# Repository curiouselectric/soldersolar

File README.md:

# Solder Solar
Design and instructions for a simple DIY solar powered torch.

# Overview
This is a very simple soldering kit to build a solar powered torch.
The unit has a small solar panel which recharges an ultra-capacitor.
There are two LEDs, one white and one red, which are powered by the energy in the ultra-capacitor.

The ultra-capacitor is 0.47F which stores enough charge for around 20 mins of white light, or around 1 hour of red light.

This kit is designed as an introduction to solar power and also soldering.

This kit can also be used as a small power supply for other projects (requiring a 3-5.5V power supply). This could be used for very low power monitoring nodes.

This repository contains:

* Instructions
* Schematics 
* PCB design
* Parts list

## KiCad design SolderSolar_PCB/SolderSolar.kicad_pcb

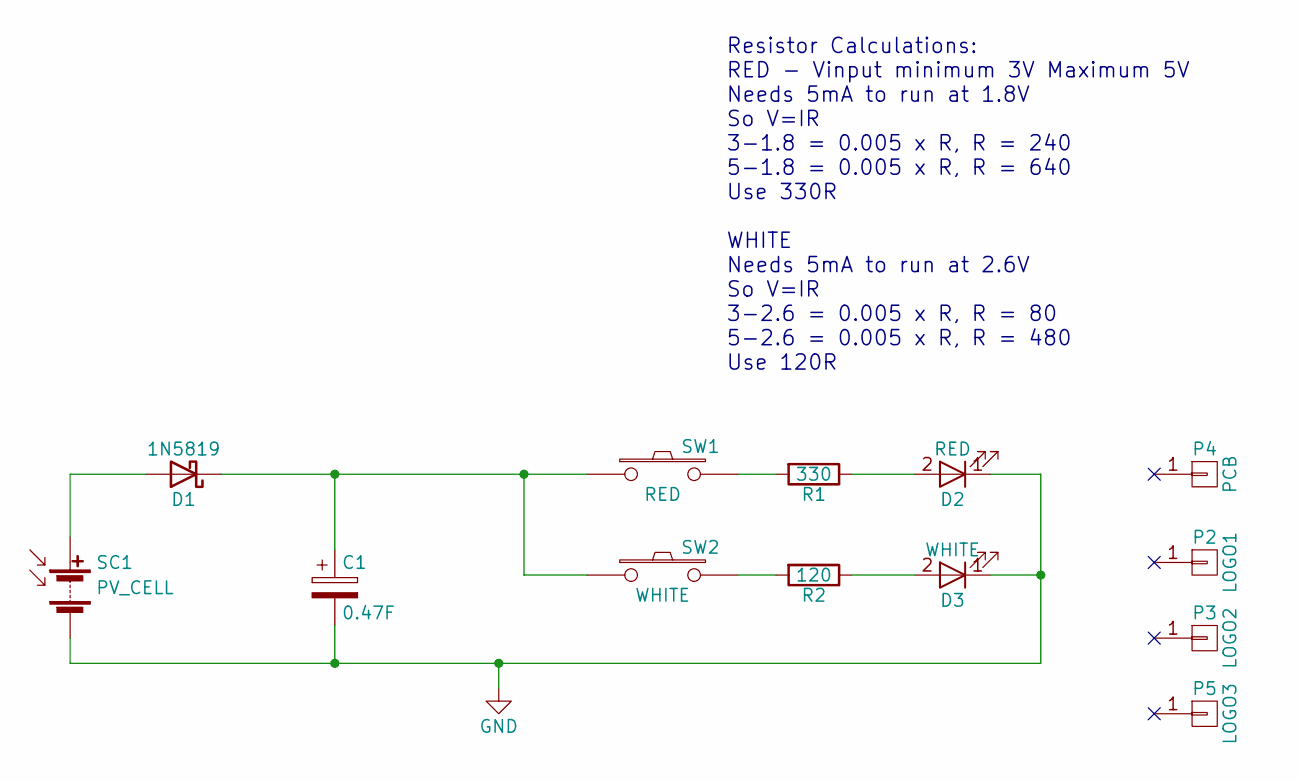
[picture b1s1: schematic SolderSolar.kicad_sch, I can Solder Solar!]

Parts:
C1: 0.47F; C_0_47F_SuperCap_3POS
D1: 1N5819; TH_Diode_1
D2: RED; TH_LED-5MM_larg_pad_90degrees
D3: WHITE; TH_LED-5MM_larg_pad_90degrees
P2: LOGO1; 2019_011_16_CuriousElectricCompany_Logo_Round_Logo_No_words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
P3: LOGO2; TCEC_Words_13mm
P4: PCB
P5: LOGO3; TCEC_Words_13mm FCu
R1: 330; TH_Resistor_1
R2: 120; TH_Resistor_1
SC1: PV_CELL; PV_50x30mm_NoOutline_v2
SW1: RED; TH_FRONT_SW
SW2: WHITE; TH_FRONT_SW

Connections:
GND: C1.2, D2.1 (K), D3.1 (K), SC1.2 (-)
unnamed: D1.2 (A), SC1.1 (+)
unnamed: C1.1, D1.1 (K), SW1.1, SW2.1
unnamed: D2.2 (A), R1.1
unnamed: D3.2 (A), R2.1
unnamed: R1.2, SW1.2
unnamed: R2.2, SW2.2

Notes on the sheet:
Resistor Calculations: RED - Vinput minimum 3V Maximum 5V Needs 5mA to run at 1.8V So V=IR 3-1.8 = 0.005 x R, R = 240 5-1.8 = 0.005 x R, R = 640 Use 330R WHITE Needs 5mA to run at 2.6V So V=IR 3-2.6 = 0.005 x R, R = 80 5-2.6 = 0.005 x R, R = 480 Use 120R

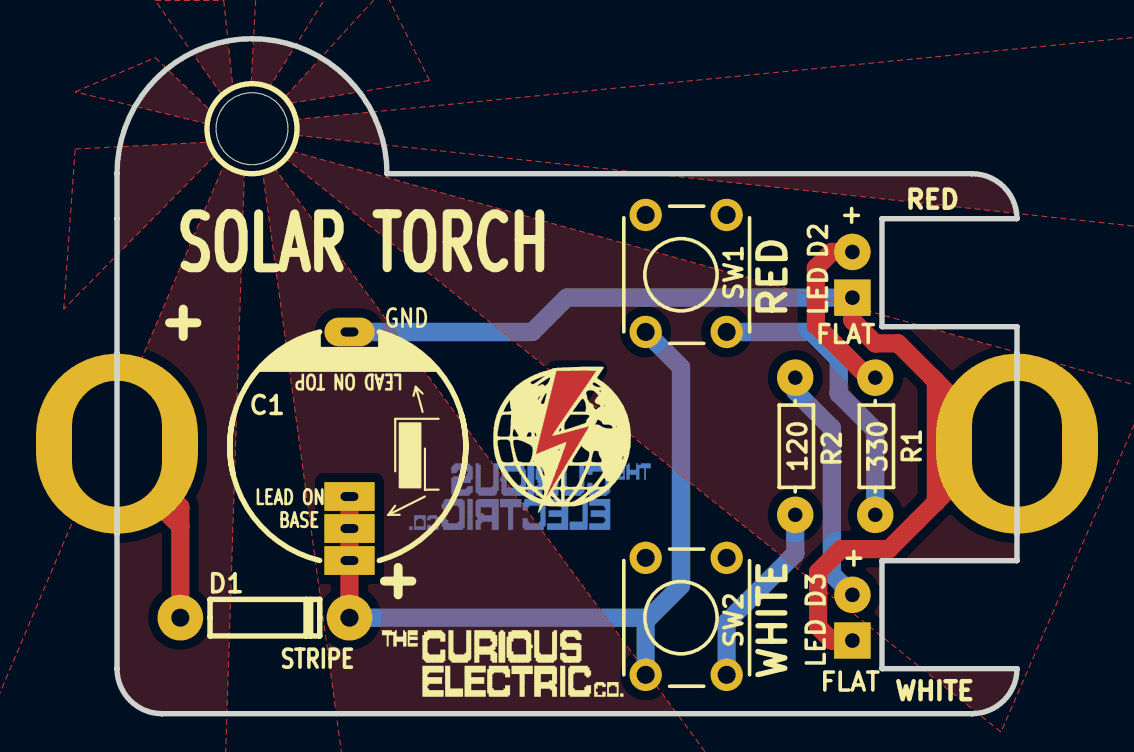
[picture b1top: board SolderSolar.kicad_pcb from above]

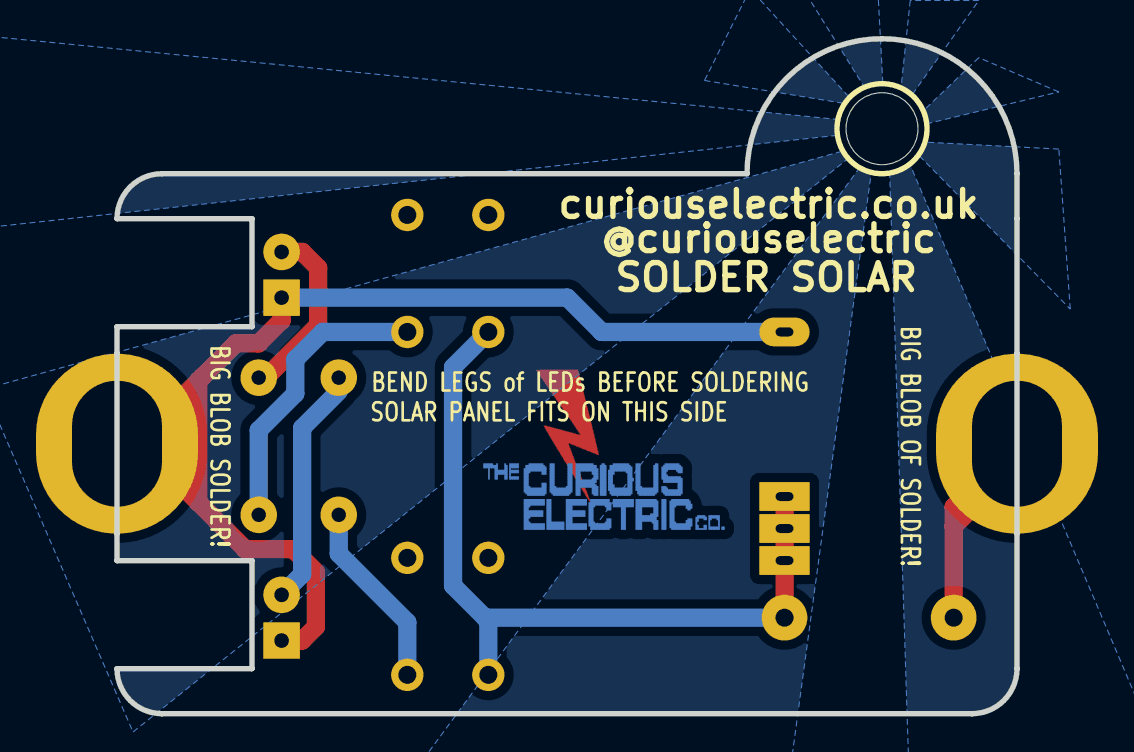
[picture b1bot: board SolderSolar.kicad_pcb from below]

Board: 2 copper layers, 50.0 x 37.5 mm, 13 parts (2 on the bottom side), 7 nets.

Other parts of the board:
P1: SOLAR_V; PV_50x30mmEdgeCut

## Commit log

2017-03-19 First Commit
    PCB files, Hardware designs
2017-03-19 Updated Names
    Removed 2017 reference
2017-03-23 Updated instructions rst. First (bad) version
2017-03-23 Updated instructions
2017-03-23 Updated instructions and rename folder
2017-03-24 Added photos for instructions
2017-03-24 added photos to rst
2017-03-24 Added photos
2017-05-13 Update SolderSolar_Instructions.rst
    s/tringles/triangles/
2021-07-04 Updated PCB for KiCAD
2023-01-22 updated to kicad 6. updated PCB
2024-06-26 Updated with new logo and instructions on PCB
2024-06-26 changed hole size for production
